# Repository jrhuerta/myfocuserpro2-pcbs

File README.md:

# myfocuserpro2-pcbs

Custom PCBs for the MyFocuserPro2 project.

There are custom PCBs using an Arduino Nano and a driver with the corresponding [MyFocuerPro2 firmare](https://sourceforge.net/projects/arduinoascomfocuserpro2diy/).

DISCLAIMER: I designed and ordered the PCBs just last night, so I haven’t had the opportunity to test them yet. I’ll confirm their functionality as soon as they arrive. Your reviews and pull requests are welcome. As with any DIY project, please proceed at your own risk.

## ULN2003

This version used with the 28BYJ-48 5V stepper powered directly from USB and a simple ULN2003 driver.
Intended to be used with an OAG or Guidescope, with 2 push bottons to retain the ability to adjust the scope manually.

## DRV8825

This version is used with a geared Nema17 and external 12V power, intended to handle heavier image trains.
It has the footprint to expand it with a set of push bottons if desired.

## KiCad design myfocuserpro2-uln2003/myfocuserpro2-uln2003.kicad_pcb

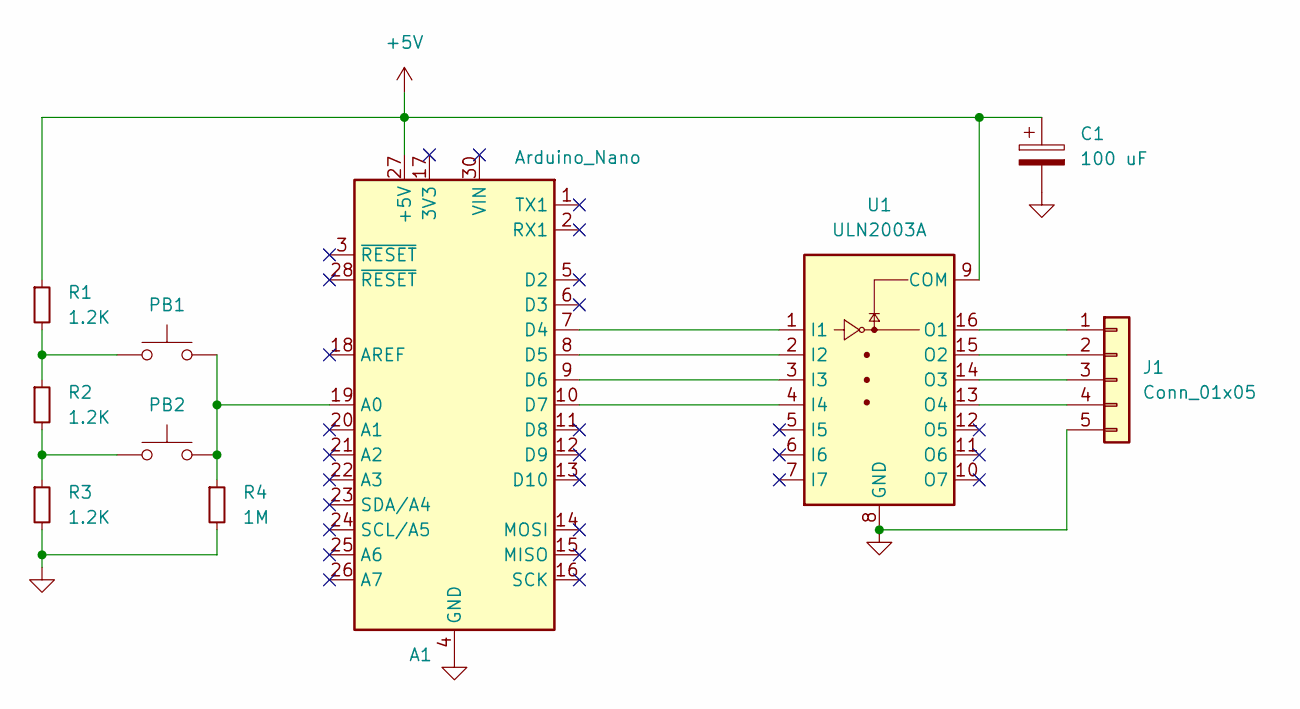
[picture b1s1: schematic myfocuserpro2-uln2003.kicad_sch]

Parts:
A1: Arduino_Nano
C1: 100 uF; CP_Radial_D6.3mm_P2.50mm
J1: Conn_01x05; PinHeader_1x05_P2.54mm_Vertical
PB1, PB2: SW_Push; SW_Tactile_SPST_Angled_PTS645Vx39-2LFS
R1, R2, R3: 1.2K; R_0603_1608Metric; LCSC C22765
R4: 1M; R_0603_1608Metric; LCSC C22935
U1: ULN2003A; SOIC-16_3.9x9.9mm_P1.27mm; LCSC C7512

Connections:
+5V: A1.27 (+5V), C1.1, R1.1, U1.9 (COM)
GND: A1.4 (GND), A1.29 (GND), C1.2, J1.5, R3.2, R4.2, U1.8 (GND)
unnamed: A1.19 (A0), PB1.2, PB2.2, R4.1
unnamed: A1.7 (D4), U1.1 (I1)
unnamed: A1.8 (D5), U1.2 (I2)
unnamed: A1.9 (D6), U1.3 (I3)
unnamed: A1.10 (D7), U1.4 (I4)
unnamed: J1.1, U1.16 (O1)
unnamed: J1.2, U1.15 (O2)
unnamed: J1.3, U1.14 (O3)
unnamed: J1.4, U1.13 (O4)
unnamed: PB1.1, R1.2, R2.1
unnamed: PB2.1, R2.2, R3.1

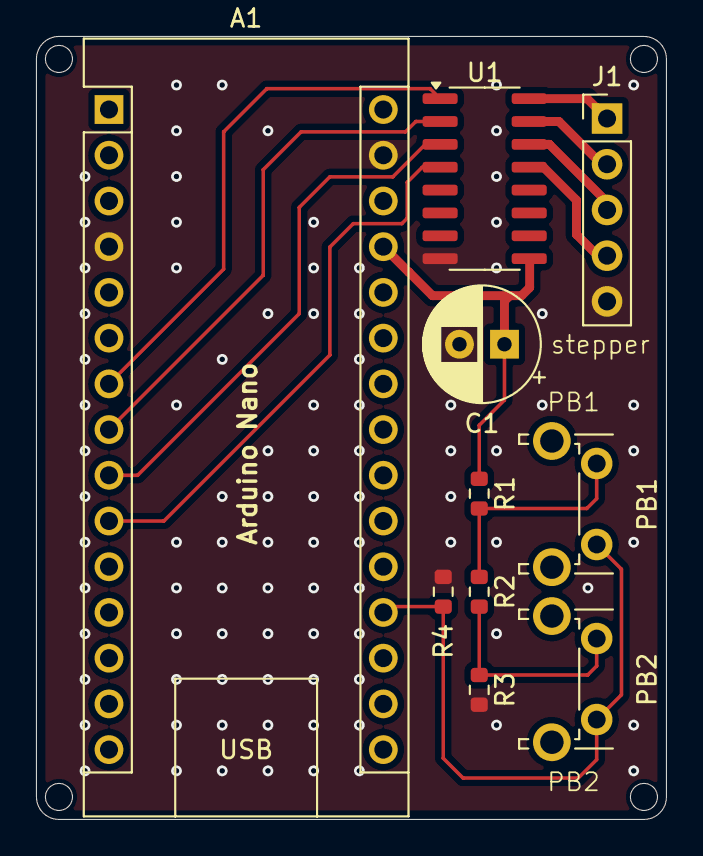
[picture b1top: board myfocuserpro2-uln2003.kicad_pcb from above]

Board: 2 copper layers, 35.0 x 43.5 mm, 14 parts (0 on the bottom side), 13 nets.

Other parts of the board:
H1, H2, H3, H4: MountingHole_Pad; MountingHole_1.5mm

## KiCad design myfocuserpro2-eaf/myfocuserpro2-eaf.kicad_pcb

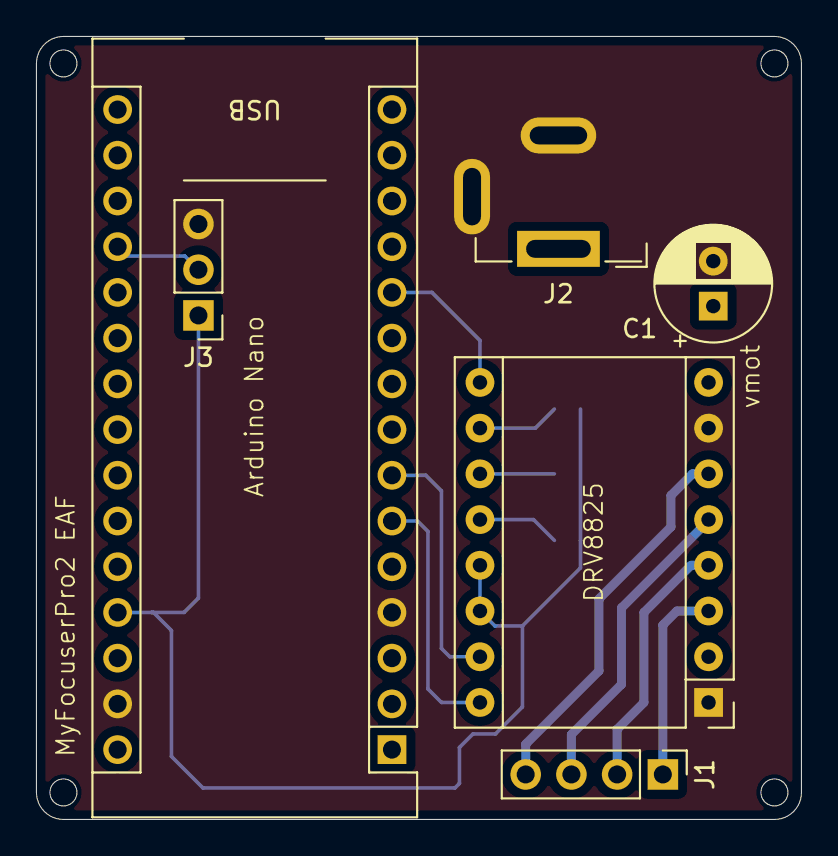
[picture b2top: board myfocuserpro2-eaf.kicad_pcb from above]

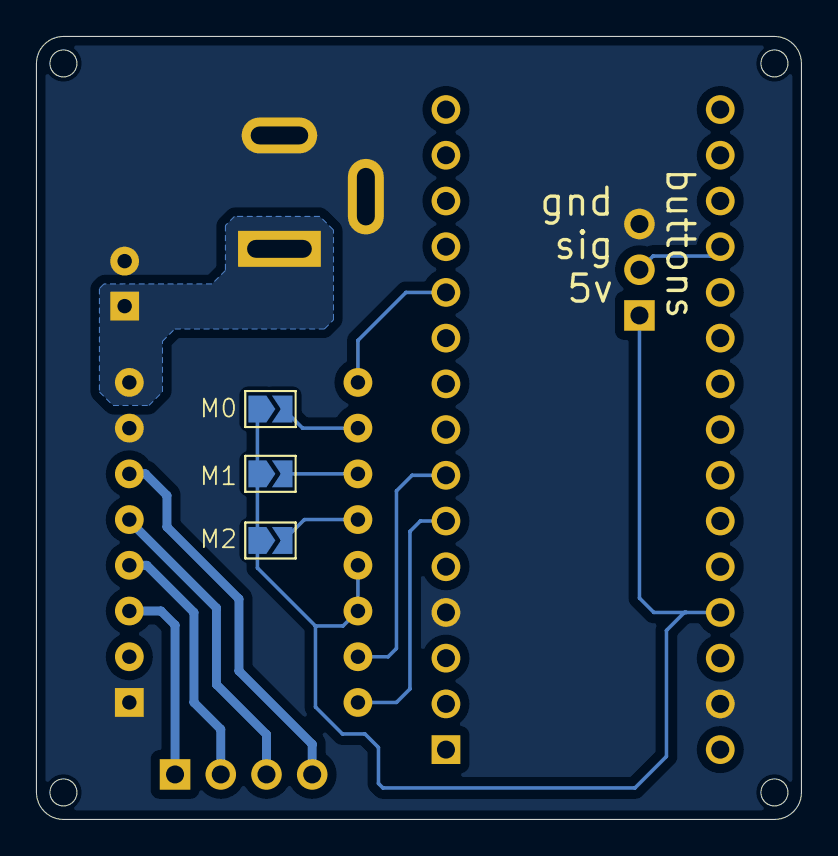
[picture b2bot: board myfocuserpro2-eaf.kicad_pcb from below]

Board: 2 copper layers, 42.5 x 43.5 mm, 13 parts (3 on the bottom side), 14 nets.

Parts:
A1: Arduino_Nano
A2: DRV8825; Pololu_Breakout-16_15.2x20.3mm
C1: 100uF; CP_Radial_D6.3mm_P2.50mm
H1, H2, H3, H4: MountingHole; MountingHole_1.5mm
J1: Conn_01x04; PinHeader_1x04_P2.54mm_Vertical
J2: 12V; BarrelJack_GCT_DCJ200-10-A_Horizontal
J3: buttons; PinHeader_1x03_P2.54mm_Vertical
JP1, JP2, JP3: SolderJumper_2_Open; SolderJumper-2_P1.3mm_Open_TrianglePad1.0x1.5mm

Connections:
+5V: A1.27 (+5V), A2.13 (~RST), A2.14 (~SLP), J3.1, JP1.1 (A), JP2.1 (A), JP3.1 (A)
/BUTTON: A1.19 (A0), J3.2
GND: A1.4 (GND), A1.29 (GND), A2.1 (GND), A2.7 (GND), C1.2, J2.2, J2.3, J3.3
unnamed: A1.6 (D3), A2.16 (DIR)
unnamed: A1.7 (D4), A2.15 (STEP)
unnamed: A1.11 (D8), A2.9 (~EN)
unnamed: A2.4 (A1), J1.2
unnamed: A2.3 (A2), J1.1
unnamed: A2.5 (B1), J1.3
unnamed: A2.6 (B2), J1.4
unnamed: A2.10 (M0), JP1.2 (B)
unnamed: A2.11 (M1), JP2.2 (B)
unnamed: A2.12 (M2), JP3.2 (B)
unnamed: A2.8 (VMOT), C1.1, J2.1

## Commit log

2025-03-30 Initial commit.
2025-03-30 Adding disclaimer.
